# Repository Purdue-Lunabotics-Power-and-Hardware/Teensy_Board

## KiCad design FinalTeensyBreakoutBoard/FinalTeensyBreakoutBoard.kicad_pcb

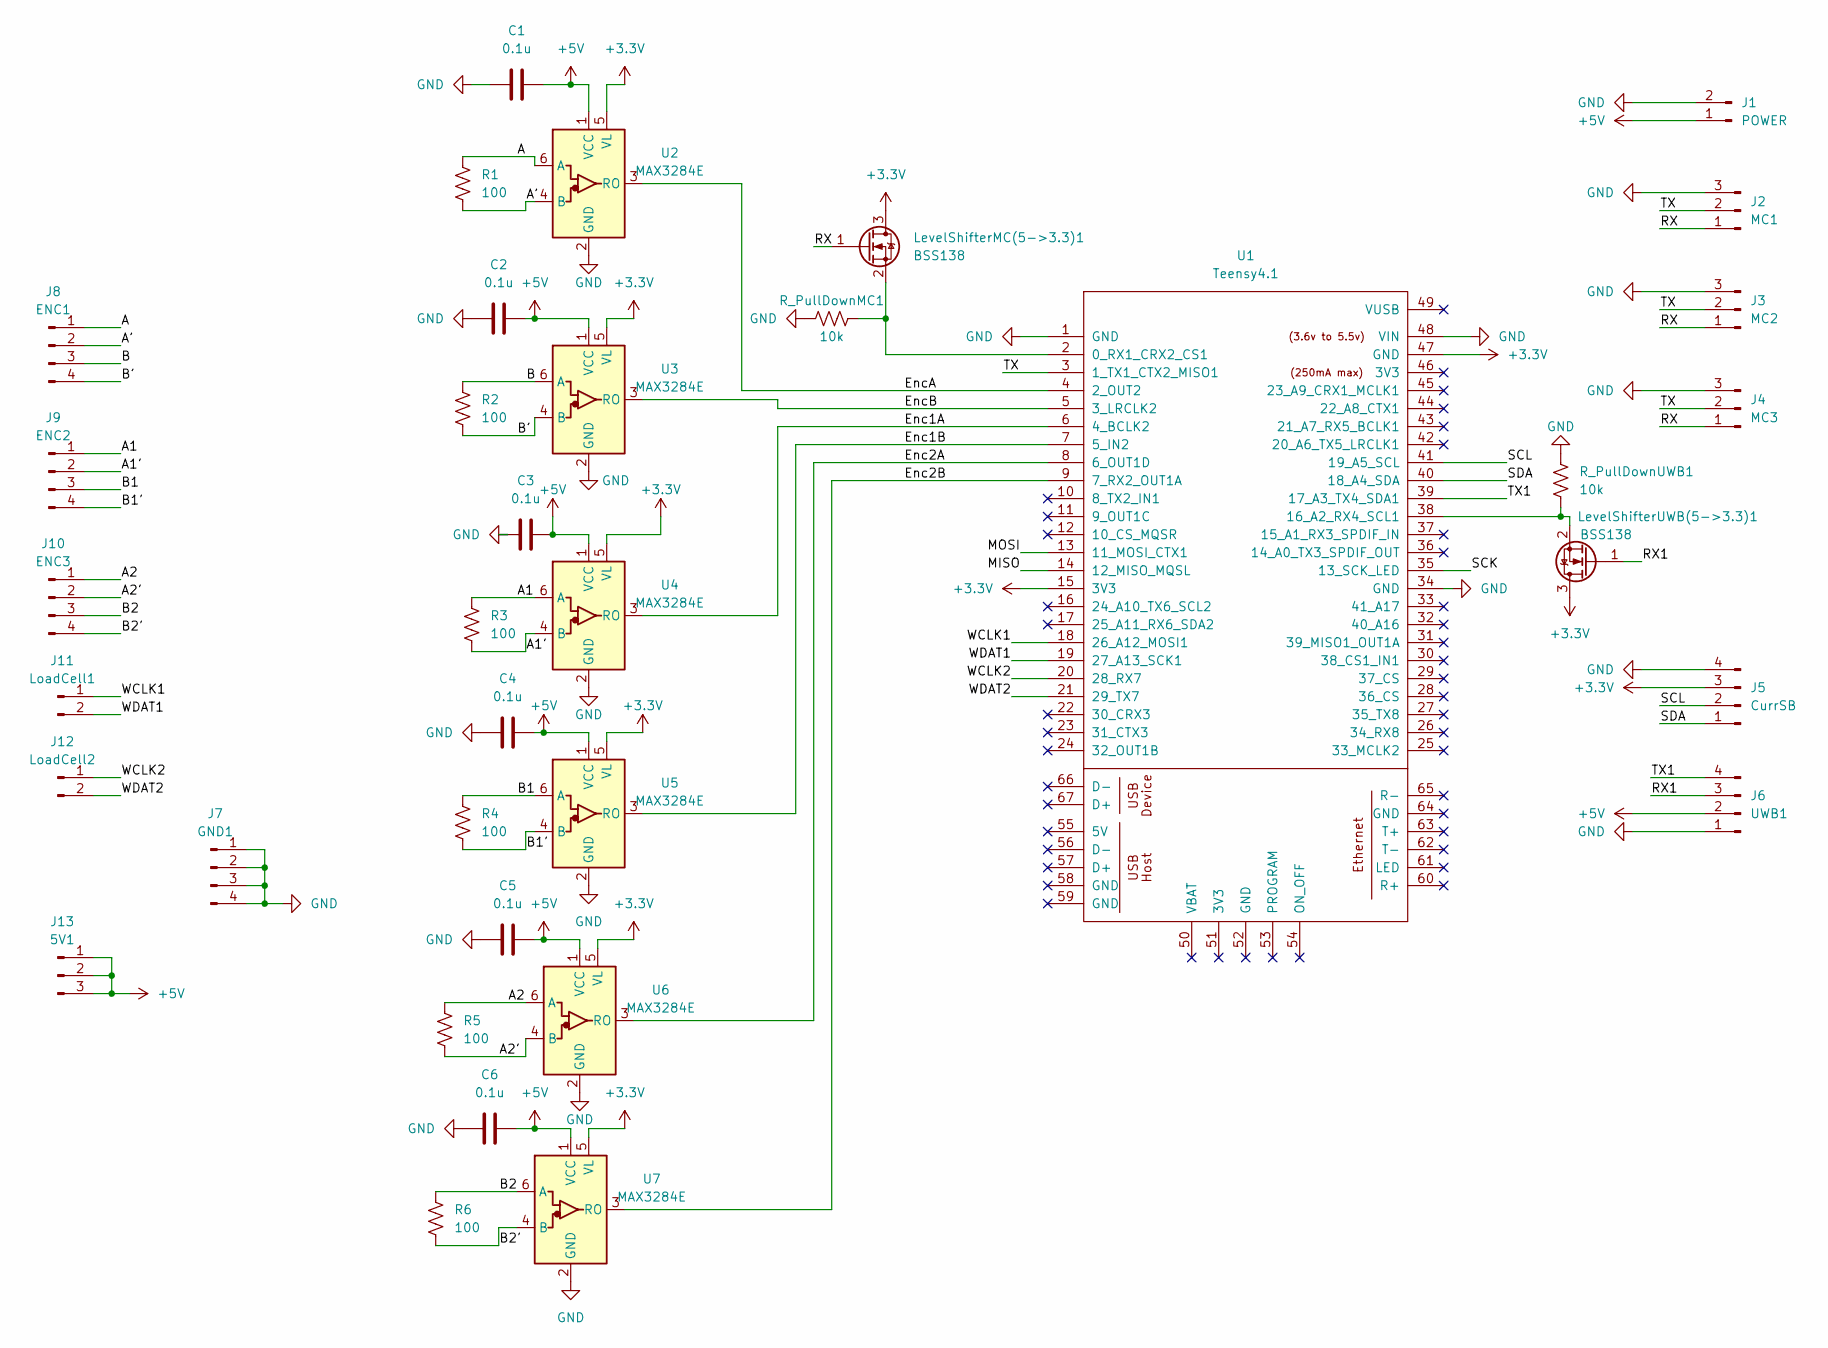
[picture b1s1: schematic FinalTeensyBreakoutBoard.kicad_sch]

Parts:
C1, C2, C3, C4, C5, C6: 0.1u; 0.1uFCap
J1: POWER; 2pinJST
J2: MC1; 3pinJST
J3: MC2; 3pinJST
J4: MC3; 3pinJST
J5: CurrSB; JST_XH_S4B-XH-A_1x04_P2.50mm_Horizontal
J6: UWB1; 4pinJST
J7: GND1; 4pinJST
J8: ENC1; 4pinJST
J9: ENC2; 4pinJST
J10: ENC3; 4pinJST
J11: LoadCell1; 2pinJST
J12: LoadCell2; 2pinJST
J13: 5V1; 3pinJST
LevelShifterMC(5->3.3)1: BSS138; SOT-23
LevelShifterUWB(5->3.3)1: BSS138; SOT-23
R1, R2, R3, R4, R5, R6: 100; 100ohmR
R_PullDownMC1: 10k; 10kOhmRes
R_PullDownUWB1: 10k; 10kOhmRes
U1: Teensy4.1; Teensy41
U2, U3, U4, U5, U6, U7: MAX3284E; SOT-23-6

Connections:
+3.3V: J5.3, LevelShifterMC(5->3.3)1.3 (D), LevelShifterUWB(5->3.3)1.3 (D), U1.15 (3V3), U1.47 (GND), U2.5 (VL), U3.5 (VL), U4.5 (VL), U5.5 (VL), U6.5 (VL), U7.5 (VL)
+5V: C1.2, C2.2, C3.2, C4.2, C5.2, C6.1, J1.1, J6.2, J13.1, J13.2, J13.3, U2.1 (VCC), U3.1 (VCC), U4.1 (VCC), U5.1 (VCC), U6.1 (VCC), U7.1 (VCC)
/A: J8.1, R1.1, U2.6 (A)
/A1: J9.1, R3.1, U4.6 (A)
/A1': J9.2, R3.2, U4.4 (B)
/A2: J10.1, R5.1, U6.6 (A)
/A2': J10.2, R5.2, U6.4 (B)
/A': J8.2, R1.2, U2.4 (B)
/B: J8.3, R2.1, U3.6 (A)
/B1: J9.3, R4.1, U5.6 (A)
/B1': J9.4, R4.2, U5.4 (B)
/B2: J10.3, R6.1, U7.6 (A)
/B2': J10.4, R6.2, U7.4 (B)
/B': J8.4, R2.2, U3.4 (B)
/Enc1A: U1.6 (4_BCLK2), U4.3 (RO)
/Enc1B: U1.7 (5_IN2), U5.3 (RO)
/Enc2A: U1.8 (6_OUT1D), U6.3 (RO)
/Enc2B: U1.9 (7_RX2_OUT1A), U7.3 (RO)
/EncA: U1.4 (2_OUT2), U2.3 (RO)
/EncB: U1.5 (3_LRCLK2), U3.3 (RO)
/MISO: U1.14 (12_MISO_MQSL)
/MOSI: U1.13 (11_MOSI_CTX1)
/RX: J2.1, J3.1, J4.1, LevelShifterMC(5->3.3)1.1 (G)
/RX1: J6.3, LevelShifterUWB(5->3.3)1.1 (G)
/SCK: U1.35 (13_SCK_LED)
/SCL: J5.2, U1.41 (19_A5_SCL)
/SDA: J5.1, U1.40 (18_A4_SDA)
/TX: J2.2, J3.2, J4.2, U1.3 (1_TX1_CTX2_MISO1)
/TX1: J6.4, U1.39 (17_A3_TX4_SDA1)
/WCLK1: J11.1, U1.18 (26_A12_MOSI1)
/WCLK2: J12.1, U1.20 (28_RX7)
/WDAT1: J11.2, U1.19 (27_A13_SCK1)
/WDAT2: J12.2, U1.21 (29_TX7)
GND: C1.1, C2.1, C3.1, C4.1, C5.1, C6.2, J1.2, J2.3, J3.3, J4.3, J5.4, J6.1, J7.1, J7.2, J7.3, J7.4, R_PullDownMC1.1, R_PullDownUWB1.1, U1.1 (GND), U1.34 (GND), U1.48 (VIN), U2.2 (GND), U3.2 (GND), U4.2 (GND), U5.2 (GND), U6.2 (GND), U7.2 (GND)
unnamed: LevelShifterMC(5->3.3)1.2 (S), R_PullDownMC1.2, U1.2 (0_RX1_CRX2_CS1)
unnamed: LevelShifterUWB(5->3.3)1.2 (S), R_PullDownUWB1.2, U1.38 (16_A2_RX4_SCL1)

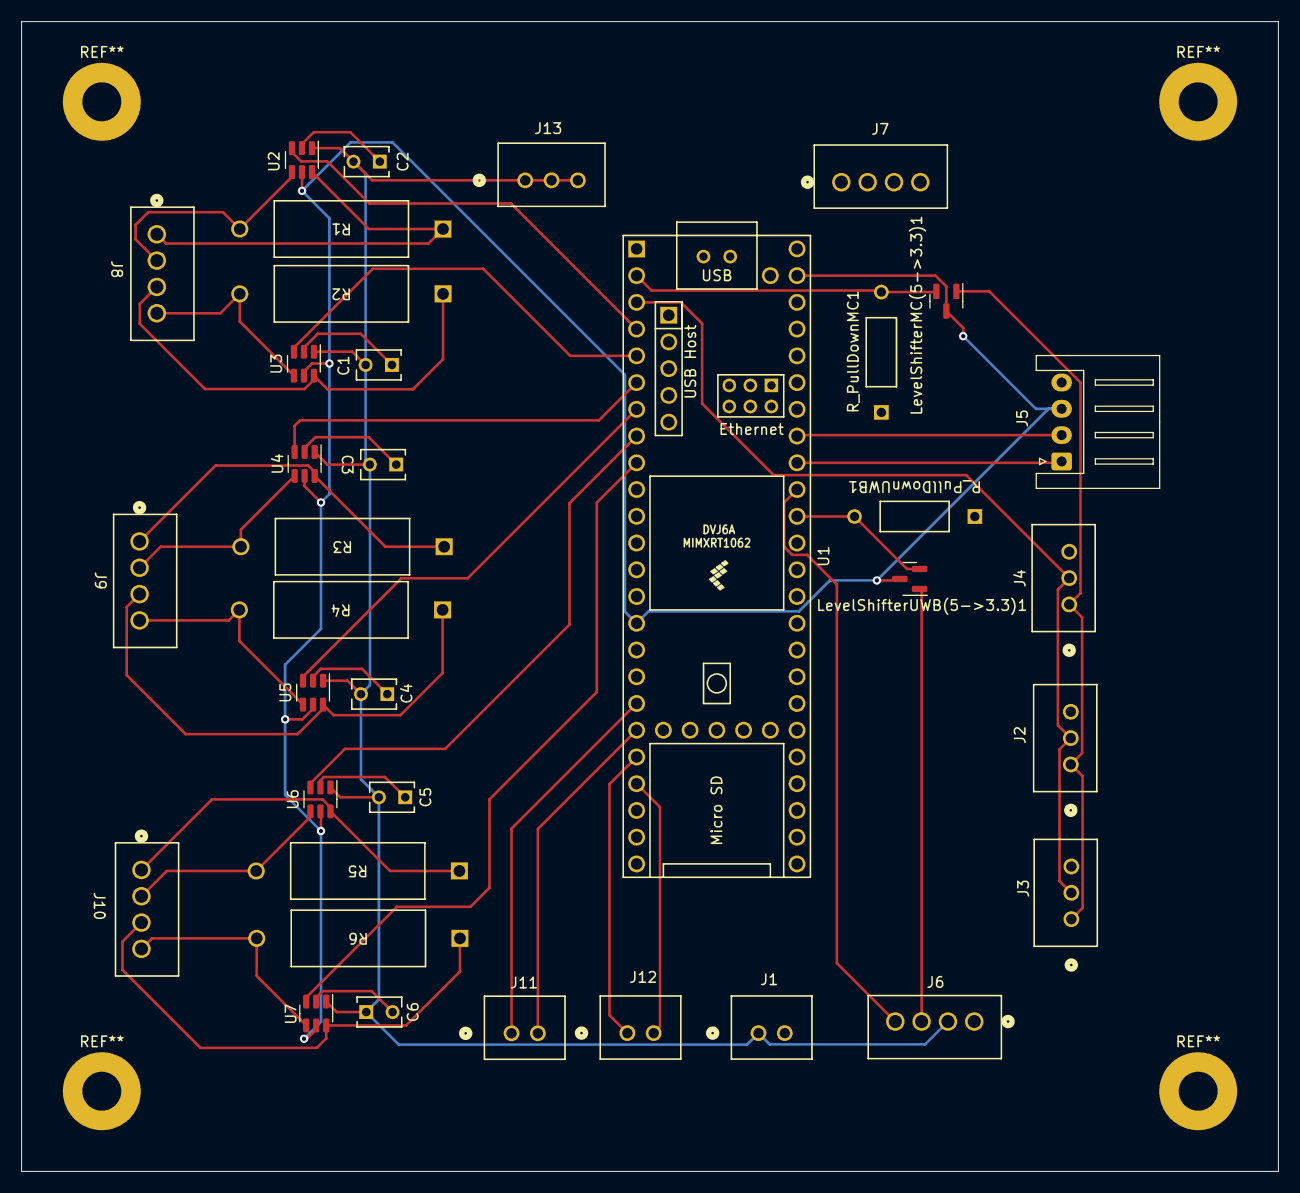
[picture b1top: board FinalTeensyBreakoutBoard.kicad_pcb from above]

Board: 2 copper layers, 119.4 x 109.2 mm, 36 parts (0 on the bottom side), 33 nets.

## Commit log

2024-01-13 finished layout
2024-01-13 tweaks
2024-01-13 added clearance
2024-01-13 new fab files
